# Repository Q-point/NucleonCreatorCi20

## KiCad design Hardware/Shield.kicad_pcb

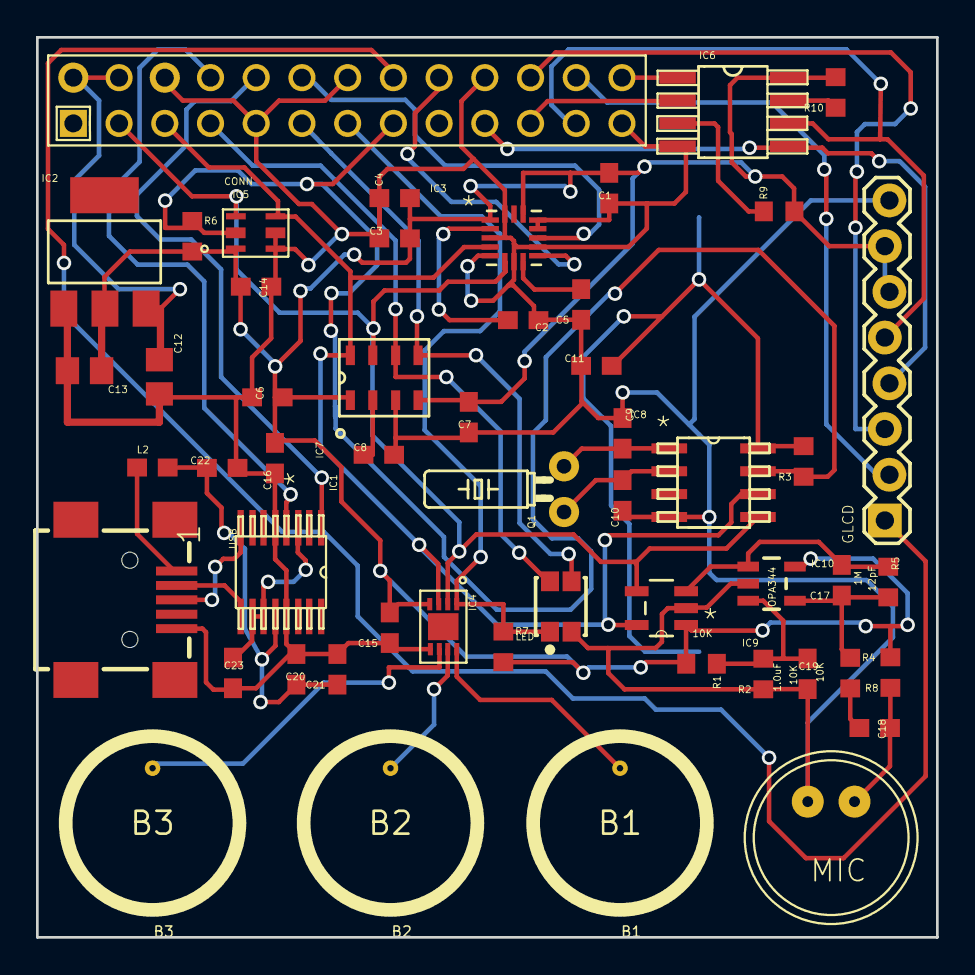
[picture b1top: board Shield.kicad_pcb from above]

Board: 2 copper layers, 50.0 x 50.0 mm, 56 parts (0 on the bottom side), 38 nets.

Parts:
B1: B1; BUTTON_PASSIVE_8MM
B2: B2; BUTTON_PASSIVE_8MM
B3: B3; BUTTON_PASSIVE_8MM
BATT: BATTERY_2032; BATT2032
C1, C2, C3, C5, C11, C14, C15, C20, C23: 0.1uF; C0603
C4, C18, C22: 4.7uF; C0603
C6, C8: 100nF; C0603
C7: 10uF; C0603
C9, C10: 12.5pF; C0603
C12, C13: 10uF; C0805
C16: 1uF; C0603
C17: 12pF; C0603
C19: 1.0uF; C0603
C21: 10nF; C0603
CE: CE_MARK5MM; CE_5MM
CONN: RASPBERRY-PI_REV1
GLCD: 1X08_LOCK
IC1: FT230XS; SOP63P600X175-16N
IC2: REG1117; SOT223
IC3: FXOS8700CQR1; QFN50P300X300X120-16N
IC4: CAP1203; TDFN-8
IC5: APDS-9300; CHIP_LED
IC6: S25FL; SO-8
IC7: MPL3115A2; DFN300X500X120-8N
IC8: MCP79400-I/SN; SOIC127P600X175-8N
IC9: MCP3221A5T-I/OT; SOT95P270X145-5N
IC10: OPA344; SOT23-5
L2: 100mA+ ferrite bead; 0603
LED: RGB; RGBLED_PLCC4
MIC: M; 9.7ELECTRET
Q1: 32Khz; TC26H
R1, R2, R4: 10K; R0603
R3, R6, R7: 10k; R0603
R5: 1M; R0603
R8: 2.2K; R0603
R9, R10: 4.7k; R0603
ROHS: ROSH_GARBAGE; ROHS_GARBAGE_5MM
USB: CONN_USB; CONN_USB_MINI-B

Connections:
5V: C12.1, CONN.2, CONN.4, IC2.3
5V+: C20.1, C21.1, C22.1, IC1.12, L2.2
ALERT: CONN.13, IC4.1, LED.1, R7.1
AUD: C17.2, IC9.3, IC10.1, R5.1
A_INT1: CONN.12, IC3.11
A_INT2: CONN.18, IC3.9
BUS_PWR: L2.1, USB.VUSB
B_INT1: CONN.7, IC7.6, LED.4
B_INT2: CONN.11, IC7.5, LED.3
CS_MEM: CONN.26, IC6.1
CS_TFT: CONN.24, GLCD.2
GND: BATT.V-, C1.1, C2.1, C3.1, C4.1, C5.1, C6.1, C7.1, C8.2, C9.1, C10.1, C11.1, C12.2, C13.2, C14.1, C15.1, C16.1, C19.2, C20.2, C21.2, C22.2, C23.2, CONN.6, CONN.9, CONN.14, CONN.20, CONN.25, GLCD.8, IC1.5, IC1.13, IC2.1, IC3.3, IC3.5, IC3.7, IC3.10, IC3.12, IC3.13, IC3.16, IC4.5, IC5.2, IC5.3, IC6.4, IC7.3, IC8.4, IC9.2, IC10.2, LED.2, MIC.-, R2.1, USB.GND
INT_LUX: CONN.15, IC5.6, IC8.7, R3.1, R6.1
MISO: CONN.21, IC6.2
MOSI: CONN.19, GLCD.4, IC6.5
unnamed: C18.1, MIC.+, R8.1
unnamed: C17.1, IC10.4, R4.1, R5.2
unnamed: C2.2, IC3.2
unnamed: C8.1, IC7.2
unnamed: C5.2, IC3.8
unnamed: BATT.V1, BATT.V2, C11.2, IC8.8, R3.2
unnamed: C10.2, IC8.2, Q1.1
unnamed: C9.2, IC8.1, Q1.2
unnamed: C18.2, R4.2
unnamed: C19.1, IC10.3, R1.1, R2.2
unnamed: IC6.3, R9.1
unnamed: IC6.7, R10.1
unnamed: IC1.8, USB.D+
unnamed: IC1.9, USB.D-
unnamed: C23.1, IC1.3, IC1.10, IC1.11
RES: CONN.16, GLCD.1
RS: CONN.22, GLCD.3
RX: CONN.10, IC1.1
SCK: CONN.23, GLCD.5, IC6.6
SCL: CONN.5, IC3.4, IC4.3, IC5.4, IC7.8, IC8.6, IC9.5
SDA: CONN.3, IC3.6, IC4.2, IC5.5, IC7.7, IC8.5, IC9.4
TX: CONN.8, IC1.4
VDD: C1.2, C3.2, C4.2, C6.2, C7.2, C13.1, C14.2, C15.2, C16.2, GLCD.6, GLCD.7, IC2.2, IC3.1, IC3.14, IC4.4, IC5.1, IC6.8, IC7.1, IC7.4, IC9.1, IC10.5, R1.2, R6.2, R7.2, R8.2, R9.2, R10.2

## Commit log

2016-05-23 :boom::camel: Added .gitattributes & .gitignore files
2016-05-23 First Commit
    First commit of the Nucleon Shield hardware and Python examples for
    Creator Ci20
2016-05-30 Updated licensing term.
    Added GPL V3 licening terms.
2016-06-15 Added BOM to Hardware folder
2016-06-15 Added BOM for hardware schematics.
2016-06-25 Last update

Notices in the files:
parts and their libraries:
License : http://creativecommons.org/licenses/by-sa/3.1/ (Creative Commons 3.1)
